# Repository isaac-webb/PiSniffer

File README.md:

# PiSniffer

In this repository, you will find a few different things:

* Schematics and board designs for our Ethernet devices. This includes both our
  attempt at a Pi HAT and the modules which we actually ordered and assembled.
* A C++ library that utilizes the `pigpio` library to interface with the
  ENC424J600 Ethernet controller over the Pi's SPI interface.
* Code to run on the LPC1768 mbed microcontroller that sniffs Ethernet packets
  off of a tapped line.
* Python code to run on the Pi that waits for the mbed to send data over USB
  and forwards packets onto the loopback interface for analysis with `tshark`.

More detailed documentation can be found [here](https://iwebb.me/PiSniffer/)

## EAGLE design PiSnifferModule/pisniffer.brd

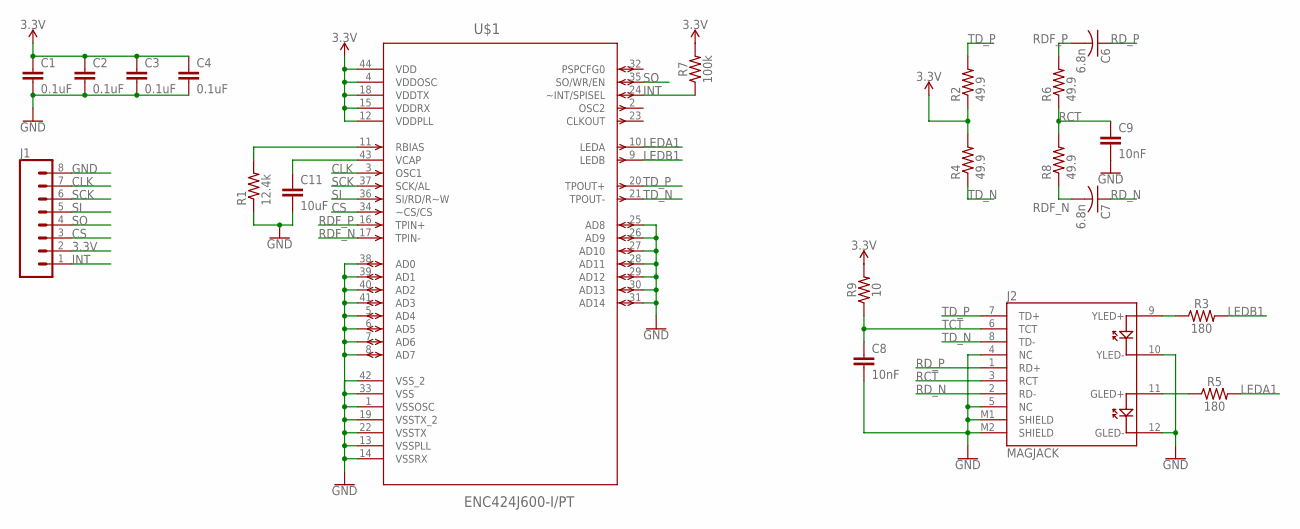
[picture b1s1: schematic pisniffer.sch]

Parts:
C1, C2, C3, C4: 0.1uF; 0603
C6, C7: 6.8n; C0603
C8, C9: 10nF; 0603
C11: 10uF; 0603
J1: CONN_08"; 1X08
J2: MAGJACK
R1: 12.4k; R0603
R2, R4, R6, R8: 49.9; R0603
R3, R5: 180; 0603
R7: 100k; 0603
R9: 10; 0603
U$1: ENC424J600-I/PT; QFP50P1200X1200X120-44N

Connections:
3.3V: C1.1, C2.1, C3.1, C4.1, J1.2, R2.1, R4.2, R7.2, R9.2, U$1.4 (VDDOSC), U$1.12 (VDDPLL), U$1.15 (VDDRX), U$1.18 (VDDTX), U$1.44 (VDD)
CLK: J1.7, U$1.3 (OSC1)
CS: J1.3, U$1.34 (~CS/CS)
GND: C1.2, C2.2, C3.2, C4.2, C8.2, C9.2, C11.2, J1.8, J2.4 (NC), J2.5 (NC), J2.10 (YLED-), J2.12 (GLED-), J2.M1 (SHIELD), J2.M2 (SHIELD), R1.1, U$1.1 (VSSOSC), U$1.5 (AD4), U$1.6 (AD5), U$1.7 (AD6), U$1.8 (AD7), U$1.13 (VSSPLL), U$1.14 (VSSRX), U$1.19 (VSSTX_2), U$1.22 (VSSTX), U$1.25 (AD8), U$1.26 (AD9), U$1.27 (AD10), U$1.28 (AD11), U$1.29 (AD12), U$1.30 (AD13), U$1.31 (AD14), U$1.33 (VSS), U$1.38 (AD0), U$1.39 (AD1), U$1.40 (AD2), U$1.41 (AD3), U$1.42 (VSS_2)
INT: J1.1, R7.1, U$1.24 (~INT/SPISEL)
LEDA1: R5.2, U$1.10 (LEDA)
LEDB1: R3.2, U$1.9 (LEDB)
unnamed: C11.1, U$1.43 (VCAP)
unnamed: R1.2, U$1.11 (RBIAS)
unnamed: J2.9 (YLED+), R3.1
unnamed: J2.11 (GLED+), R5.1
RCT: C9.1, J2.3 (RCT), R6.1, R8.2
RDF_N: C7.2, R8.1, U$1.17 (TPIN-)
RDF_P: C6.2, R6.2, U$1.16 (TPIN+)
RD_N: C7.1, J2.2 (RD-)
RD_P: C6.1, J2.1 (RD+)
SCK: J1.6, U$1.37 (SCK/AL)
SI: J1.5, U$1.36 (SI/RD/R~W)
SO: J1.4, U$1.35 (SO/WR/EN)
TCT: C8.1, J2.6 (TCT), R9.1
TD_N: J2.8 (TD-), R4.1, U$1.21 (TPOUT-)
TD_P: J2.7 (TD+), R2.2, U$1.20 (TPOUT+)

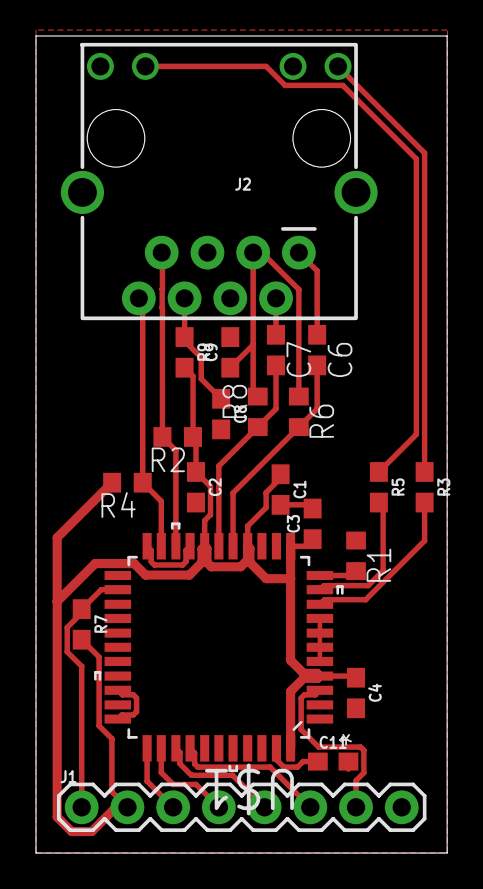
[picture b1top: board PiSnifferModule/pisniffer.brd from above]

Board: 2 copper layers, 22.8 x 45.4 mm, 21 parts (0 on the bottom side), 22 nets.

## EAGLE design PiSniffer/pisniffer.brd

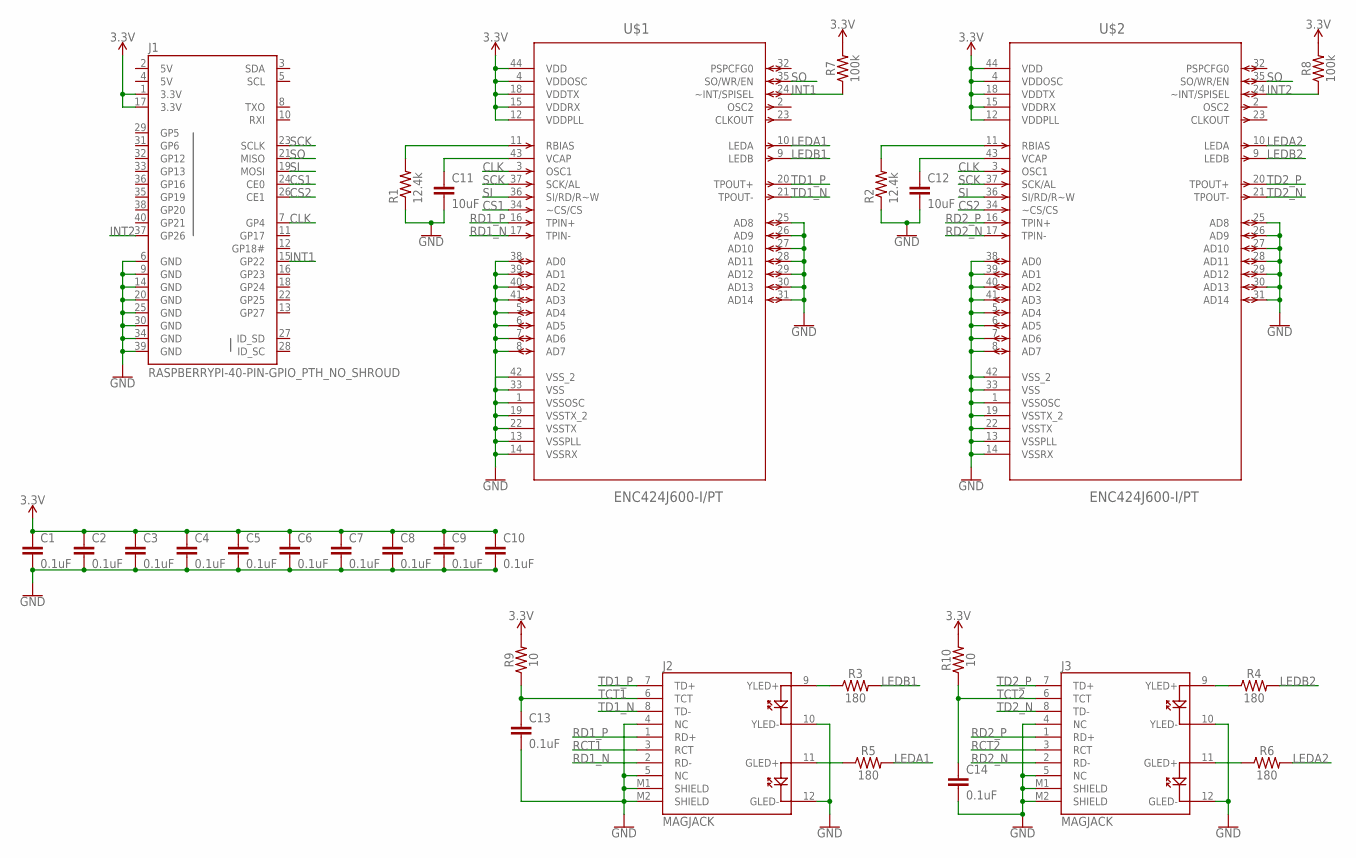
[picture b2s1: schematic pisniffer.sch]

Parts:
C1, C2, C3, C4, C5, C6, C7, C8, C9, C10, C13, C14: 0.1uF; 0603
C11, C12: 10uF; 0603
J1: RASPBERRYPI-40-PIN-GPIO_PTH_NO_SHROUD; 2X20
J2, J3: MAGJACK
R1, R2: 12.4k; R0603
R3, R4, R5, R6: 180; 0603
R7, R8: 100k; 0603
R9, R10: 10; 0603
U$1, U$2: ENC424J600-I/PT; QFP50P1200X1200X120-44N

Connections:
3.3V: C1.1, C2.1, C3.1, C4.1, C5.1, C6.1, C7.1, C8.1, C9.1, C10.1, J1.1 (3.3V), J1.17 (3.3V), R7.2, R8.2, R9.2, R10.2, U$1.4 (VDDOSC), U$1.12 (VDDPLL), U$1.15 (VDDRX), U$1.18 (VDDTX), U$1.44 (VDD), U$2.4 (VDDOSC), U$2.12 (VDDPLL), U$2.15 (VDDRX), U$2.18 (VDDTX), U$2.44 (VDD)
5V: J1.2 (5V), J1.4 (5V)
CLK: J1.7 (GP4), U$1.3 (OSC1), U$2.3 (OSC1)
CS1: J1.24 (CE0), U$1.34 (~CS/CS)
CS2: J1.26 (CE1), U$2.34 (~CS/CS)
GND: C1.2, C2.2, C3.2, C4.2, C5.2, C6.2, C7.2, C8.2, C9.2, C10.2, C11.2, C12.2, C13.2, C14.2, J1.6 (GND), J1.9 (GND), J1.14 (GND), J1.20 (GND), J1.25 (GND), J1.30 (GND), J1.34 (GND), J1.39 (GND), J2.4 (NC), J2.5 (NC), J2.10 (YLED-), J2.12 (GLED-), J2.M1 (SHIELD), J2.M2 (SHIELD), J3.4 (NC), J3.5 (NC), J3.10 (YLED-), J3.12 (GLED-), J3.M1 (SHIELD), J3.M2 (SHIELD), R1.1, R2.1, U$1.1 (VSSOSC), U$1.5 (AD4), U$1.6 (AD5), U$1.7 (AD6), U$1.8 (AD7), U$1.13 (VSSPLL), U$1.14 (VSSRX), U$1.19 (VSSTX_2), U$1.22 (VSSTX), U$1.25 (AD8), U$1.26 (AD9), U$1.27 (AD10), U$1.28 (AD11), U$1.29 (AD12), U$1.30 (AD13), U$1.31 (AD14), U$1.33 (VSS), U$1.38 (AD0), U$1.39 (AD1), U$1.40 (AD2), U$1.41 (AD3), U$1.42 (VSS_2), U$2.1 (VSSOSC), U$2.5 (AD4), U$2.6 (AD5), U$2.7 (AD6), U$2.8 (AD7), U$2.13 (VSSPLL), U$2.14 (VSSRX), U$2.19 (VSSTX_2), U$2.22 (VSSTX), U$2.25 (AD8), U$2.26 (AD9), U$2.27 (AD10), U$2.28 (AD11), U$2.29 (AD12), U$2.30 (AD13), U$2.31 (AD14), U$2.33 (VSS), U$2.38 (AD0), U$2.39 (AD1), U$2.40 (AD2), U$2.41 (AD3), U$2.42 (VSS_2)
INT1: J1.15 (GP22), R7.1, U$1.24 (~INT/SPISEL)
INT2: J1.37 (GP26), R8.1, U$2.24 (~INT/SPISEL)
LEDA1: R5.2, U$1.10 (LEDA)
LEDA2: R6.2, U$2.10 (LEDA)
LEDB1: R3.2, U$1.9 (LEDB)
LEDB2: R4.2, U$2.9 (LEDB)
unnamed: C11.1, U$1.43 (VCAP)
unnamed: C12.1, U$2.43 (VCAP)
unnamed: R2.2, U$2.11 (RBIAS)
unnamed: R1.2, U$1.11 (RBIAS)
unnamed: J2.9 (YLED+), R3.1
unnamed: J2.11 (GLED+), R5.1
unnamed: J3.9 (YLED+), R4.1
unnamed: J3.11 (GLED+), R6.1
RCT1: J2.3 (RCT)
RCT2: J3.3 (RCT)
RD1_N: J2.2 (RD-), U$1.17 (TPIN-)
RD1_P: J2.1 (RD+), U$1.16 (TPIN+)
RD2_N: J3.2 (RD-), U$2.17 (TPIN-)
RD2_P: J3.1 (RD+), U$2.16 (TPIN+)
SCK: J1.23 (SCLK), U$1.37 (SCK/AL), U$2.37 (SCK/AL)
SI: J1.19 (MOSI), U$1.36 (SI/RD/R~W), U$2.36 (SI/RD/R~W)
SO: J1.21 (MISO), U$1.35 (SO/WR/EN), U$2.35 (SO/WR/EN)
TCT1: C13.1, J2.6 (TCT), R9.1
TCT2: C14.1, J3.6 (TCT), R10.1
TD1_N: J2.8 (TD-), U$1.21 (TPOUT-)
TD1_P: J2.7 (TD+), U$1.20 (TPOUT+)
TD2_N: J3.8 (TD-), U$2.21 (TPOUT-)
TD2_P: J3.7 (TD+), U$2.20 (TPOUT+)

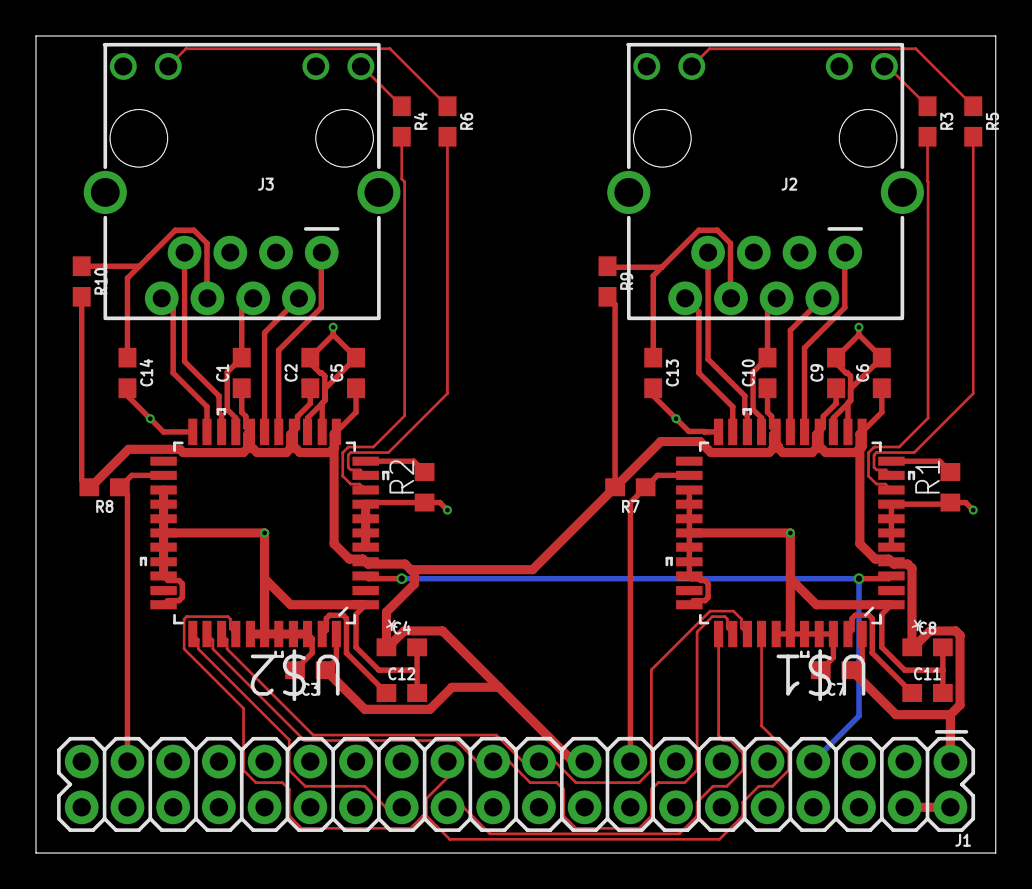
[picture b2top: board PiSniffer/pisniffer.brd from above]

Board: 2 copper layers, 53.3 x 45.4 mm, 29 parts (0 on the bottom side), 33 nets.

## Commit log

2019-04-29 Add initial project files
2019-04-29 Add basic README
2019-04-29 Remove compiled files
2019-04-29 Add GitHub Pages directory and dummy index page
2019-04-29 Set theme jekyll-theme-hacker
2019-04-29 Add pictures for website, documentation introduction
2019-04-29 Fix image link
2019-04-29 Fix image link, attempt 2
2019-04-29 Fix image link, take 3
2019-04-29 Add all pictures, more content
2019-04-29 Update README, controller library code, and finish documentation for HAT design
2019-04-29 Add mbed code
2019-04-29 Move source files to root
2019-04-29 Finish documentation up to demo explanations
2019-04-29 Finish up first draft of documentation
2019-05-29 Create CNAME

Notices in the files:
parts and their libraries:
SparkFun-Connectors: Licensing: Creative Commons ShareAlike 4.0 International - https://creativecommons.org/licenses/by-sa/4.0
